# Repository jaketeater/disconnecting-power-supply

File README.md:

# Disconnecting Power Supply #

The disconnecting power supply (for lack of a better name) is a simple way to make a project running on a battery for a long period of time.

This project was inspired by [this video by Ralph S Bacon](https://www.youtube.com/watch?v=g1rbIG2BO0U) and [this blog post by Indrek Luuk](https://circuitjournal.com/arduino-auto-power-off). 

This works with projects that: 

- run periodically (not constantly)
- are triggered by an outside input, like a button press
- are compatible with the supply's voltage and amperage limitations

## Usage Example ##

This project could be used to make a battery powered device that sends an alert when mail is delivered. 

For wiring, the input power is connected to a 9v battery. Then the output power and ground are connected to the micro controller. Connect the power supply's keep-alive to a pin on the micro controller. Connect the trigger pin and the ground pin to a switch that closes when the mailbox door is opened (ex: a gravity switch). 

Next, program a micro controller to send a message when it is powered on. Then add a line so that the first thing your program does is raise the keep-alive pin high to make sure the power supply remains on, and then at the end of your program, after the message is sent, add code to lower the keep-alive pin to 0v to disconnect the battery.

## How it works ##

To understand how this circuit works, see [this video by Ralph S Bacon](https://www.youtube.com/watch?v=g1rbIG2BO0U) or [this blog post by Indrek Luuk](https://circuitjournal.com/arduino-auto-power-off). 

The project adds an RC circuit to give the microcontroller time to boot, allowing for very short button presses to turn the power supply on. This allows, for example, for reed switches (like [this one from Adafruit](https://www.adafruit.com/product/2384) with a contact time of ~2ms) to be used.

# Version Naming #

`<AMPS>-<INPUT-VOLTAGE-MAX>-<INPUT-VOLTAGE-MIN>-<OUTPUT-VOLTAGE>-<LED>`

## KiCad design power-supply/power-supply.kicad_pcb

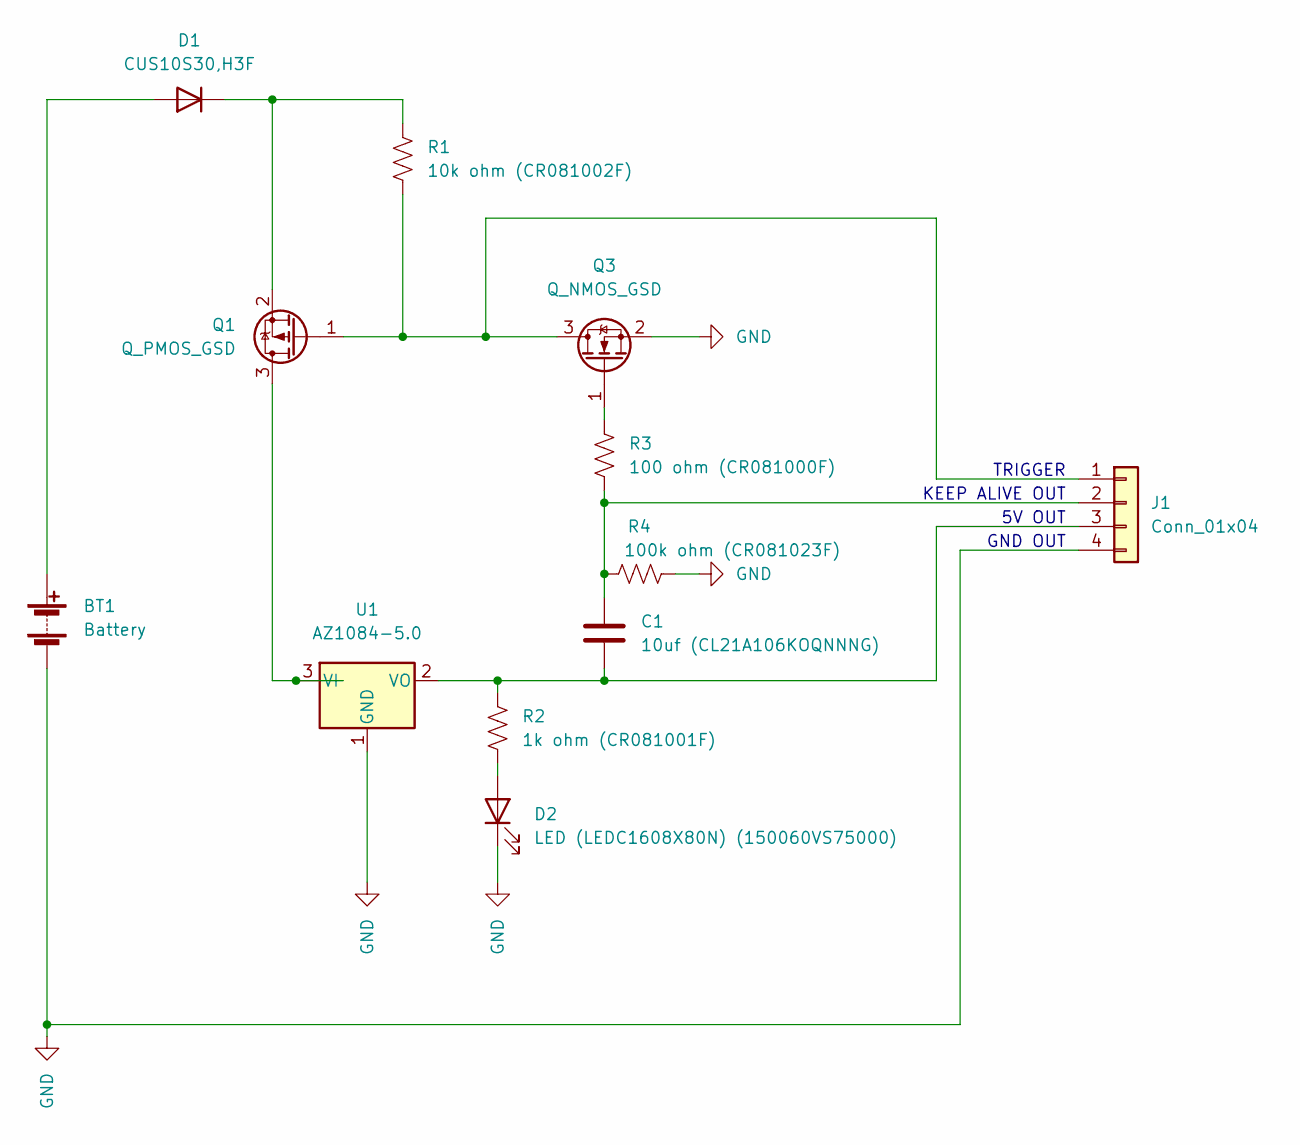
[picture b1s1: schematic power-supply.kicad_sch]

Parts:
BT1: Battery; PinHeader_1x02_P2.54mm_Vertical
C1: 10uf (CL21A106KOQNNNG); C_0805_2012Metric
D1: CUS10S30,H3F; D_SOD-323
D2: LED (LEDC1608X80N) (150060VS75000); LED_0603_1608Metric
J1: Conn_01x04; PinHeader_1x04_P2.54mm_Vertical
Q1: Q_PMOS_GSD; SOT-323_SC-70
Q3: Q_NMOS_GSD; SOT-323_SC-70
R1: 10k ohm (CR081002F); R_1206_3216Metric
R2: 1k ohm (CR081001F); R_1206_3216Metric
R3: 100 ohm (CR081000F); R_1206_3216Metric
R4: 100k ohm (CR081023F); R_1206_3216Metric
U1: AZ1084-5.0; TO-252-2

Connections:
GND: BT1.2 (-), D2.1 (K), J1.4, Q3.2 (S), R4.2, U1.1 (GND)
unnamed: BT1.1 (+), D1.2 (A)
unnamed: C1.1, J1.2, R3.2, R4.1
unnamed: C1.2, J1.3, R2.2, U1.2 (VO)
unnamed: D1.1 (K), Q1.2 (S), R1.1
unnamed: J1.1, Q1.1 (G), Q3.3 (D), R1.2
unnamed: Q1.3 (D), U1.3 (VI)
unnamed: Q3.1 (G), R3.1
unnamed: D2.2 (A), R2.1

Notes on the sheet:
5V OUT
KEEP ALIVE OUT
TRIGGER
GND OUT

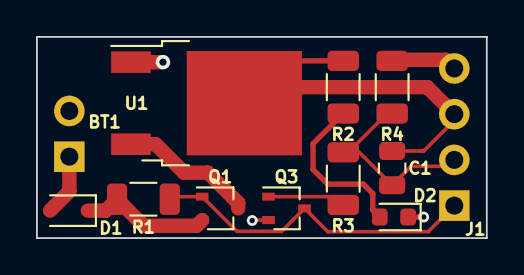
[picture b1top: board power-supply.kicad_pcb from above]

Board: 2 copper layers, 25.0 x 11.2 mm, 12 parts (0 on the bottom side), 9 nets.

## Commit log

2022-12-21 Added kicad files
2022-12-22 Rearranged onto a smaller board
2022-12-22 decreased width to slightly under 25mm
2022-12-22 misc
2022-12-24 updated fab notes
2022-12-24 init work on readme
